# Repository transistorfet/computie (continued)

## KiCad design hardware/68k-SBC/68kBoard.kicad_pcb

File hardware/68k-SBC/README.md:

68k-SBC
=======

Status: Built & Tested

Latest: Rev.2

### About
A single board computer with DIP packaged chips.  The only programmable chip is the flash memory, which can
be written in-circuit using the Ardunio-based supervisor shield.

[Revision 2 Notes & Errata](revisions/68kBoard-rev2-errata.txt)

[Revision 2 Schematic](revisions/68kBoard-rev2.pdf)

[Revision 2 Gerbers](revisions/68kBoard-rev2.zip)

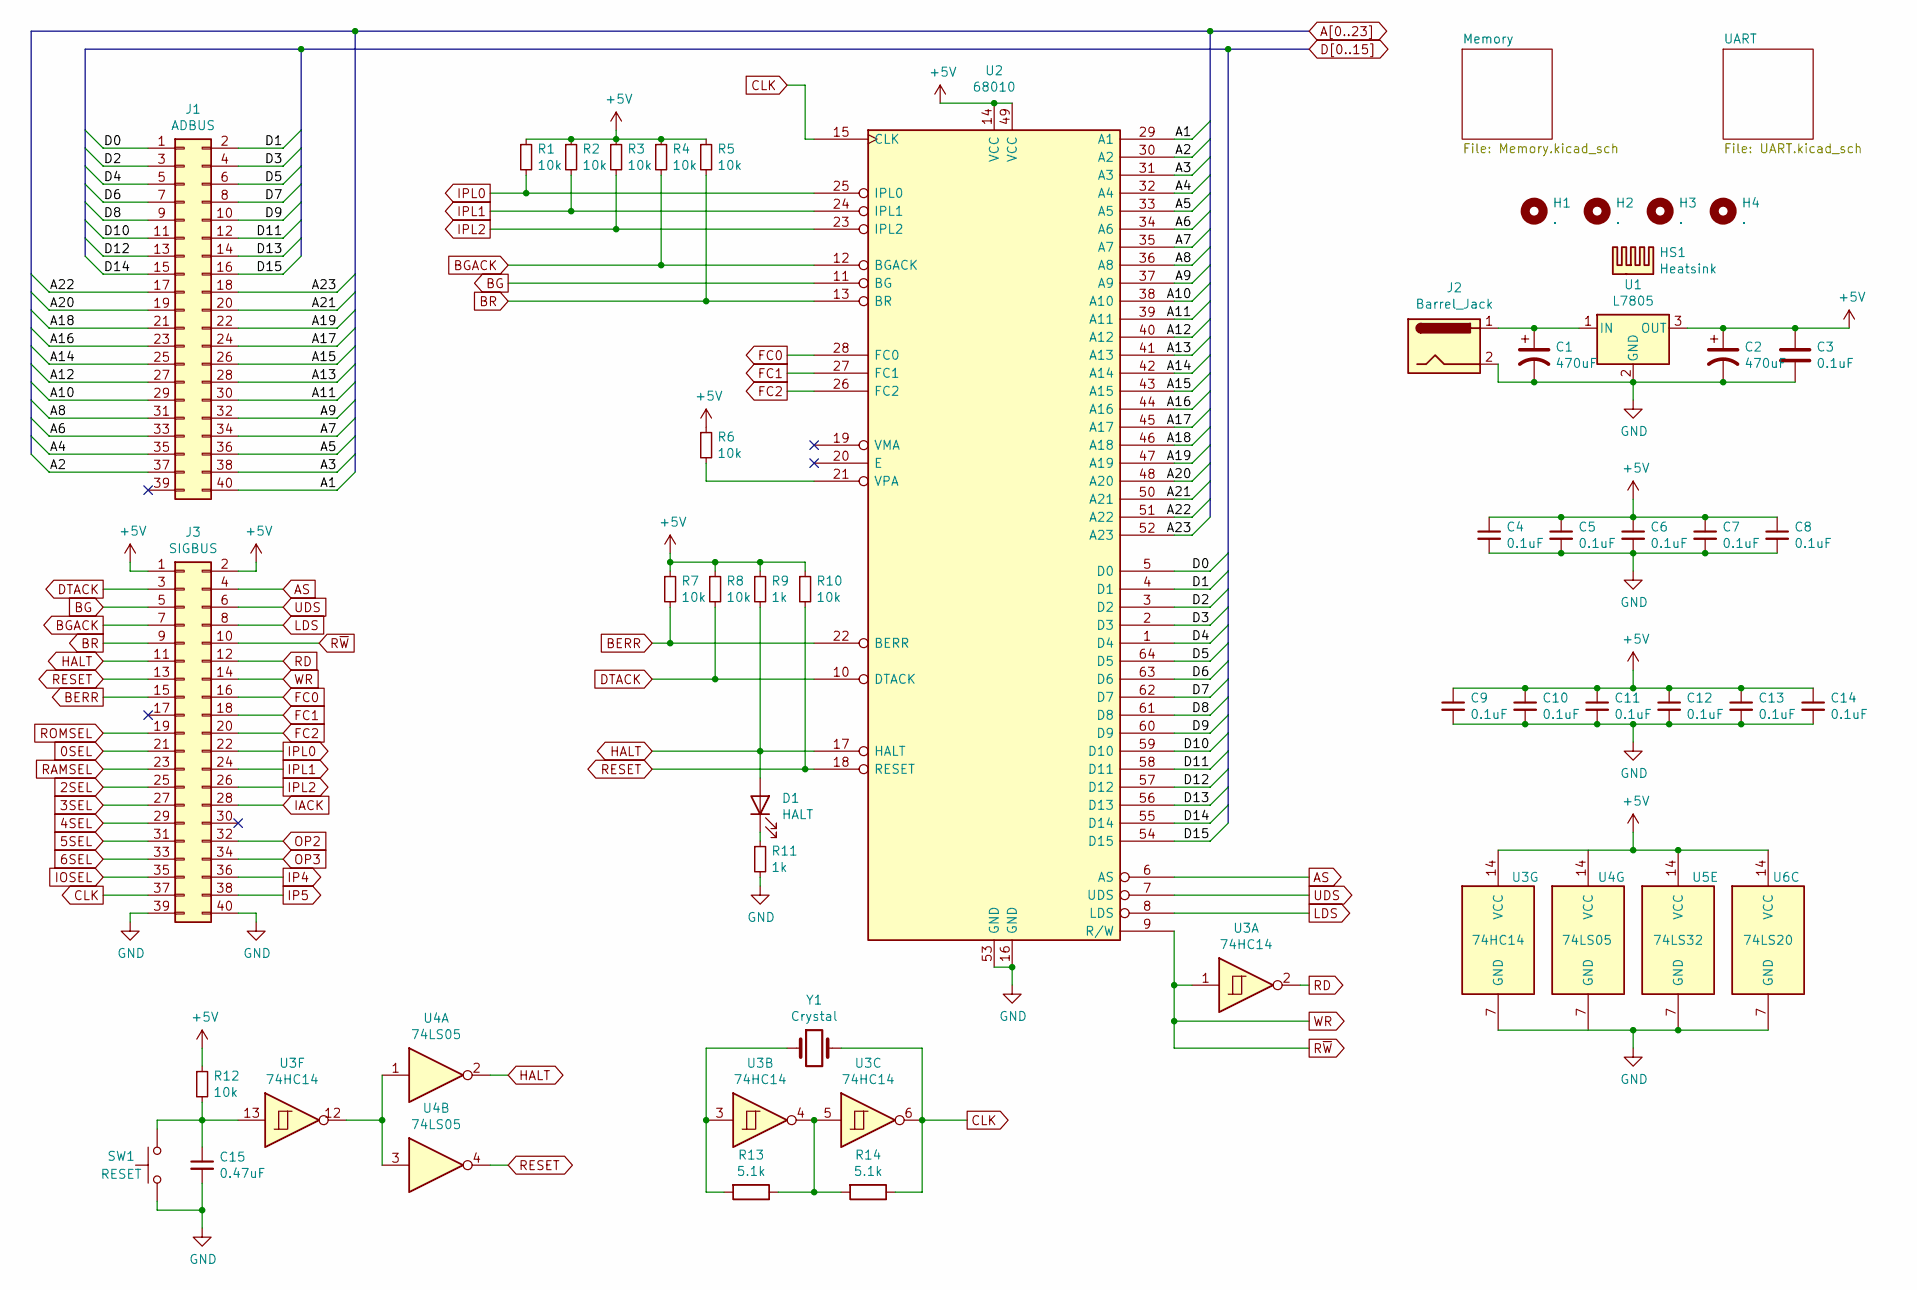
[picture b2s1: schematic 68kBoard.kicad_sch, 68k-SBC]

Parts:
C1, C2: 470uF; CP_Radial_D10.0mm_P5.00mm
C3, C4, C5, C6, C7, C8, C9, C10, C11, C12, C13, C14: 0.1uF; C_Disc_D3.0mm_W2.0mm_P2.50mm
C15: 0.47uF; C_Disc_D3.0mm_W2.0mm_P2.50mm
D1: HALT; LED_D5.0mm
H1, H2, H3, H4: .; MountingHole_2.7mm_Pad_Via
HS1: Heatsink; Heatsink_Fischer_SK104-STC-STIC_35x13mm_2xDrill2.5mm
J1: ADBUS; PinHeader_2x20_P2.54mm_Vertical
J2: Barrel_Jack; BarrelJack_Horizontal
J3: SIGBUS; PinHeader_2x20_P2.54mm_Vertical
R1, R2, R3, R4, R5, R6, R7, R8, R10, R12: 10k; R_Axial_DIN0207_L6.3mm_D2.5mm_P7.62mm_Horizontal
R9, R11: 1k; R_Axial_DIN0207_L6.3mm_D2.5mm_P7.62mm_Horizontal
R13, R14: 5.1k; R_Axial_DIN0207_L6.3mm_D2.5mm_P7.62mm_Horizontal
SW1: RESET; SW_PUSH_6mm
U1: L7805; TO-220-3_Vertical
U2: 68010; DIP-64_W22.86mm_Socket_LongPads
U3: 74HC14; DIP-14_W7.62mm_LongPads
U4: 74LS05; DIP-14_W7.62mm_LongPads
U5: 74LS32; DIP-14_W7.62mm_LongPads
U6: 74LS20; DIP-14_W7.62mm_LongPads
Y1: Crystal; Crystal_HC49-4H_Vertical

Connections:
0SEL: J3.21; also elsewhere on the board
2SEL: J3.25; also elsewhere on the board
3SEL: J3.27; also elsewhere on the board
4SEL: J3.29; also elsewhere on the board
5SEL: J3.31; also elsewhere on the board
6SEL: J3.33; also elsewhere on the board
+5V: C2.1, C3.1, C4.1, C5.1, C6.1, C7.1, C8.1, C9.1, C10.1, C11.1, C12.1, C13.1, C14.1, J3.1, J3.2, R1.1, R2.1, R3.1, R4.1, R5.1, R6.1, R7.1, R8.1, R9.1, R10.1, R12.1, U1.3 (OUT), U2.14 (VCC), U2.49 (VCC), U3.14 (VCC), U4.14 (VCC), U5.14 (VCC), U6.14 (VCC); also elsewhere on the board
A1: J1.40, U2.29 (A1); also elsewhere on the board
A2: J1.37, U2.30 (A2); also elsewhere on the board
A3: J1.38, U2.31 (A3); also elsewhere on the board
A4: J1.35, U2.32 (A4); also elsewhere on the board
A5: J1.36, U2.33 (A5); also elsewhere on the board
A6: J1.33, U2.34 (A6); also elsewhere on the board
A7: J1.34, U2.35 (A7); also elsewhere on the board
A8: J1.31, U2.36 (A8); also elsewhere on the board
A9: J1.32, U2.37 (A9); also elsewhere on the board
A10: J1.29, U2.38 (A10); also elsewhere on the board
A11: J1.30, U2.39 (A11); also elsewhere on the board
A12: J1.27, U2.40 (A12); also elsewhere on the board
A13: J1.28, U2.41 (A13); also elsewhere on the board
A14: J1.25, U2.42 (A14); also elsewhere on the board
A15: J1.26, U2.43 (A15); also elsewhere on the board
A16: J1.23, U2.44 (A16); also elsewhere on the board
A17: J1.24, U2.45 (A17); also elsewhere on the board
A18: J1.21, U2.46 (A18); also elsewhere on the board
A19: J1.22, U2.47 (A19); also elsewhere on the board
A20: J1.19, U2.48 (A20); also elsewhere on the board
A21: J1.20, U2.50 (A21); also elsewhere on the board
A22: J1.17, U2.51 (A22); also elsewhere on the board
A23: J1.18, U2.52 (A23); also elsewhere on the board
AS: J3.4, U2.6 (AS); also elsewhere on the board
BERR: J3.15, R7.2, U2.22 (BERR)
BG: J3.5, U2.11 (BG)
BGACK: J3.7, R4.2, U2.12 (BGACK)
BR: J3.9, R5.2, U2.13 (BR)
CLK: J3.37, R14.1, U2.15 (CLK), U3.6, Y1.2
D0: J1.1, U2.5 (D0); also elsewhere on the board
D1: J1.2, U2.4 (D1); also elsewhere on the board
D2: J1.3, U2.3 (D2); also elsewhere on the board
D3: J1.4, U2.2 (D3); also elsewhere on the board
D4: J1.5, U2.1 (D4); also elsewhere on the board
D5: J1.6, U2.64 (D5); also elsewhere on the board
D6: J1.7, U2.63 (D6); also elsewhere on the board
D7: J1.8, U2.62 (D7); also elsewhere on the board
D8: J1.9, U2.61 (D8); also elsewhere on the board
D9: J1.10, U2.60 (D9); also elsewhere on the board
D10: J1.11, U2.59 (D10); also elsewhere on the board
D11: J1.12, U2.58 (D11); also elsewhere on the board
D12: J1.13, U2.57 (D12); also elsewhere on the board
D13: J1.14, U2.56 (D13); also elsewhere on the board
D14: J1.15, U2.55 (D14); also elsewhere on the board
D15: J1.16, U2.54 (D15); also elsewhere on the board
DTACK: J3.3, R8.2, U2.10 (DTACK); also elsewhere on the board
FC0: J3.16, U2.28 (FC0); also elsewhere on the board
FC1: J3.18, U2.27 (FC1); also elsewhere on the board
FC2: J3.20, U2.26 (FC2); also elsewhere on the board
GND: C1.2, C2.2, C3.2, C4.2, C5.2, C6.2, C7.2, C8.2, C9.2, C10.2, C11.2, C12.2, C13.2, C14.2, C15.2, J2.2, J3.39, J3.40, R11.2, SW1.1, U1.2 (GND), U2.16 (GND), U2.53 (GND), U3.7 (GND), U4.7 (GND), U5.7 (GND), U6.7 (GND); also elsewhere on the board
HALT: D1.2 (A), J3.11, R9.2, U2.17 (HALT), U4.2
IACK: J3.28; also elsewhere on the board
IOSEL: J3.35; also elsewhere on the board
IP4: J3.36; also elsewhere on the board
IP5: J3.38; also elsewhere on the board
IPL0: J3.22, R1.2, U2.25 (IPL0)
IPL1: J3.24, R2.2, U2.24 (IPL1); also elsewhere on the board
IPL2: J3.26, R3.2, U2.23 (IPL2)
LDS: J3.8, U2.8 (LDS); also elsewhere on the board
unnamed: C1.1, J2.1, U1.1 (IN)
unnamed: C15.1, R12.2, SW1.2, U3.13
unnamed: D1.1 (K), R11.1
unnamed: R6.2, U2.21 (VPA)
unnamed: R13.1, R14.2, U3.4, U3.5
unnamed: R13.2, U3.3, Y1.1
unnamed: U3.12, U4.1, U4.3
OP2: J3.32; also elsewhere on the board
OP3: J3.34; also elsewhere on the board
RAMSEL: J3.23; also elsewhere on the board
RD: J3.12, U3.2; also elsewhere on the board
RESET: J3.13, R10.2, U2.18 (RESET), U4.4; also elsewhere on the board
ROMSEL: J3.19; also elsewhere on the board
R~W: J3.10, J3.14, U2.9 (R/W), U3.1; also elsewhere on the board
UDS: J3.6, U2.7 (UDS); also elsewhere on the board

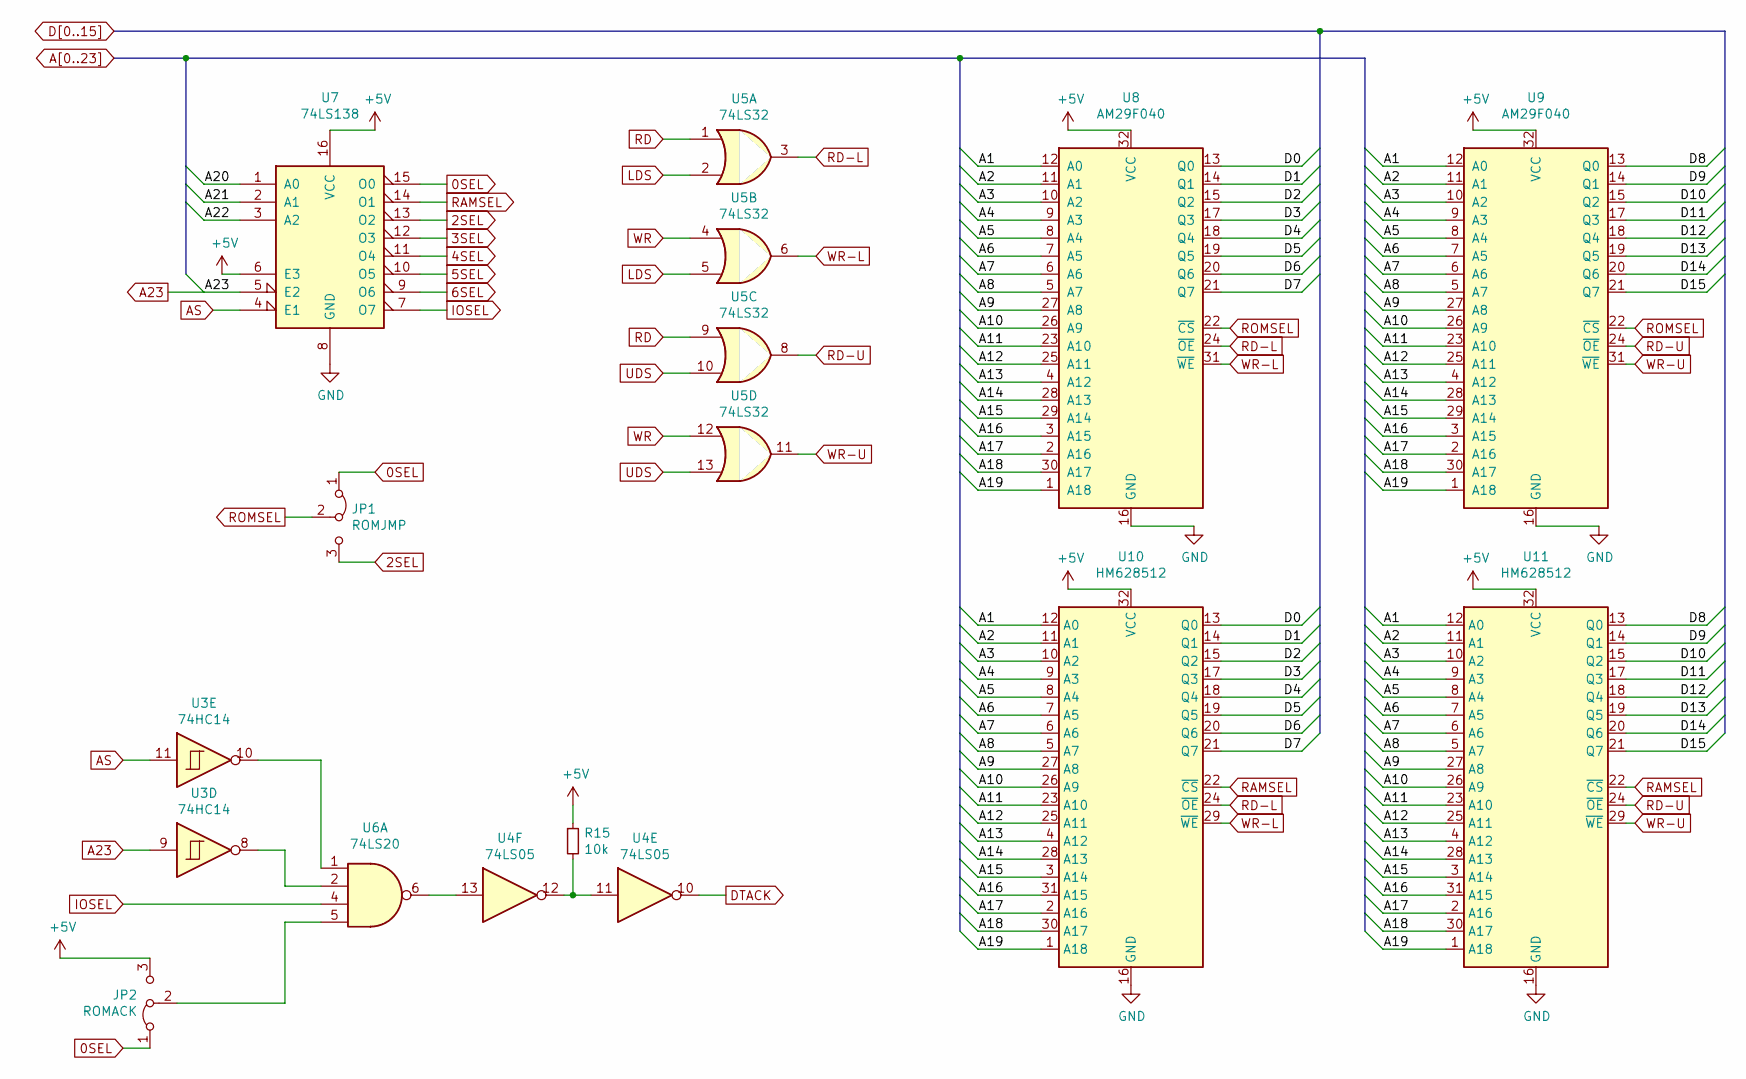
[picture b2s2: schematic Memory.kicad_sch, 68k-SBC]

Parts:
JP1: ROMJMP; PinHeader_1x03_P2.54mm_Vertical
JP2: ROMACK; PinHeader_1x03_P2.54mm_Vertical
R15: 10k; R_Axial_DIN0207_L6.3mm_D2.5mm_P7.62mm_Horizontal
U3: 74HC14; DIP-14_W7.62mm_LongPads
U4: 74LS05; DIP-14_W7.62mm_LongPads
U5: 74LS32; DIP-14_W7.62mm_LongPads
U6: 74LS20; DIP-14_W7.62mm_LongPads
U7: 74LS138; DIP-16_W7.62mm_LongPads
U8, U9: AM29F040; DIP-32_W15.24mm_Socket_LongPads
U10, U11: HM628512; DIP-32_W15.24mm_Socket_LongPads

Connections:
0SEL: JP1.1 (A), JP2.1 (A), U7.15 (O0); also elsewhere on the board
2SEL: JP1.3 (B), U7.13 (O2); also elsewhere on the board
3SEL: U7.12 (O3); also elsewhere on the board
4SEL: U7.11 (O4); also elsewhere on the board
5SEL: U7.10 (O5); also elsewhere on the board
6SEL: U7.9 (O6); also elsewhere on the board
+5V: JP2.3 (B), R15.1, U7.6 (E3), U7.16 (VCC), U8.32 (VCC), U9.32 (VCC), U10.32 (VCC), U11.32 (VCC); also elsewhere on the board
A1: U8.12 (A0), U9.12 (A0), U10.12 (A0), U11.12 (A0); also elsewhere on the board
A2: U8.11 (A1), U9.11 (A1), U10.11 (A1), U11.11 (A1); also elsewhere on the board
A3: U8.10 (A2), U9.10 (A2), U10.10 (A2), U11.10 (A2); also elsewhere on the board
A4: U8.9 (A3), U9.9 (A3), U10.9 (A3), U11.9 (A3); also elsewhere on the board
A5: U8.8 (A4), U9.8 (A4), U10.8 (A4), U11.8 (A4); also elsewhere on the board
A6: U8.7 (A5), U9.7 (A5), U10.7 (A5), U11.7 (A5); also elsewhere on the board
A7: U8.6 (A6), U9.6 (A6), U10.6 (A6), U11.6 (A6); also elsewhere on the board
A8: U8.5 (A7), U9.5 (A7), U10.5 (A7), U11.5 (A7); also elsewhere on the board
A9: U8.27 (A8), U9.27 (A8), U10.27 (A8), U11.27 (A8); also elsewhere on the board
A10: U8.26 (A9), U9.26 (A9), U10.26 (A9), U11.26 (A9); also elsewhere on the board
A11: U8.23 (A10), U9.23 (A10), U10.23 (A10), U11.23 (A10); also elsewhere on the board
A12: U8.25 (A11), U9.25 (A11), U10.25 (A11), U11.25 (A11); also elsewhere on the board
A13: U8.4 (A12), U9.4 (A12), U10.4 (A12), U11.4 (A12); also elsewhere on the board
A14: U8.28 (A13), U9.28 (A13), U10.28 (A13), U11.28 (A13); also elsewhere on the board
A15: U8.29 (A14), U9.29 (A14), U10.3 (A14), U11.3 (A14); also elsewhere on the board
A16: U8.3 (A15), U9.3 (A15), U10.31 (A15), U11.31 (A15); also elsewhere on the board
A17: U8.2 (A16), U9.2 (A16), U10.2 (A16), U11.2 (A16); also elsewhere on the board
A18: U8.30 (A17), U9.30 (A17), U10.30 (A17), U11.30 (A17); also elsewhere on the board
A19: U8.1 (A18), U9.1 (A18), U10.1 (A18), U11.1 (A18); also elsewhere on the board
A20: U7.1 (A0); also elsewhere on the board
A21: U7.2 (A1); also elsewhere on the board
A22: U7.3 (A2); also elsewhere on the board
A23: U3.9, U7.5 (E2); also elsewhere on the board
AS: U3.11, U7.4 (E1); also elsewhere on the board
D0: U8.13 (Q0), U10.13 (Q0); also elsewhere on the board
D1: U8.14 (Q1), U10.14 (Q1); also elsewhere on the board
D2: U8.15 (Q2), U10.15 (Q2); also elsewhere on the board
D3: U8.17 (Q3), U10.17 (Q3); also elsewhere on the board
D4: U8.18 (Q4), U10.18 (Q4); also elsewhere on the board
D5: U8.19 (Q5), U10.19 (Q5); also elsewhere on the board
D6: U8.20 (Q6), U10.20 (Q6); also elsewhere on the board
D7: U8.21 (Q7), U10.21 (Q7); also elsewhere on the board
D8: U9.13 (Q0), U11.13 (Q0); also elsewhere on the board
D9: U9.14 (Q1), U11.14 (Q1); also elsewhere on the board
D10: U9.15 (Q2), U11.15 (Q2); also elsewhere on the board
D11: U9.17 (Q3), U11.17 (Q3); also elsewhere on the board
D12: U9.18 (Q4), U11.18 (Q4); also elsewhere on the board
D13: U9.19 (Q5), U11.19 (Q5); also elsewhere on the board
D14: U9.20 (Q6), U11.20 (Q6); also elsewhere on the board
D15: U9.21 (Q7), U11.21 (Q7); also elsewhere on the board
DTACK: U4.10; also elsewhere on the board
GND: U7.8 (GND), U8.16 (GND), U9.16 (GND), U10.16 (GND), U11.16 (GND); also elsewhere on the board
IOSEL: U6.4, U7.7 (O7); also elsewhere on the board
LDS: U5.2, U5.5; also elsewhere on the board
unnamed: JP2.2 (C), U6.5
unnamed: R15.2, U4.11, U4.12
unnamed: U3.8, U6.2
unnamed: U3.10, U6.1
unnamed: U4.13, U6.6
RAMSEL: U7.14 (O1), U10.22 (~CS), U11.22 (~CS); also elsewhere on the board
RD: U5.1, U5.9; also elsewhere on the board
RD-L: U5.3, U8.24 (~OE), U10.24 (~OE)
RD-U: U5.8, U9.24 (~OE), U11.24 (~OE)
ROMSEL: JP1.2 (C), U8.22 (~CS), U9.22 (~CS); also elsewhere on the board
R~W: U5.4, U5.12; also elsewhere on the board
UDS: U5.10, U5.13; also elsewhere on the board
WR-L: U5.6, U8.31 (~WE), U10.29 (~WE)
WR-U: U5.11, U9.31 (~WE), U11.29 (~WE)

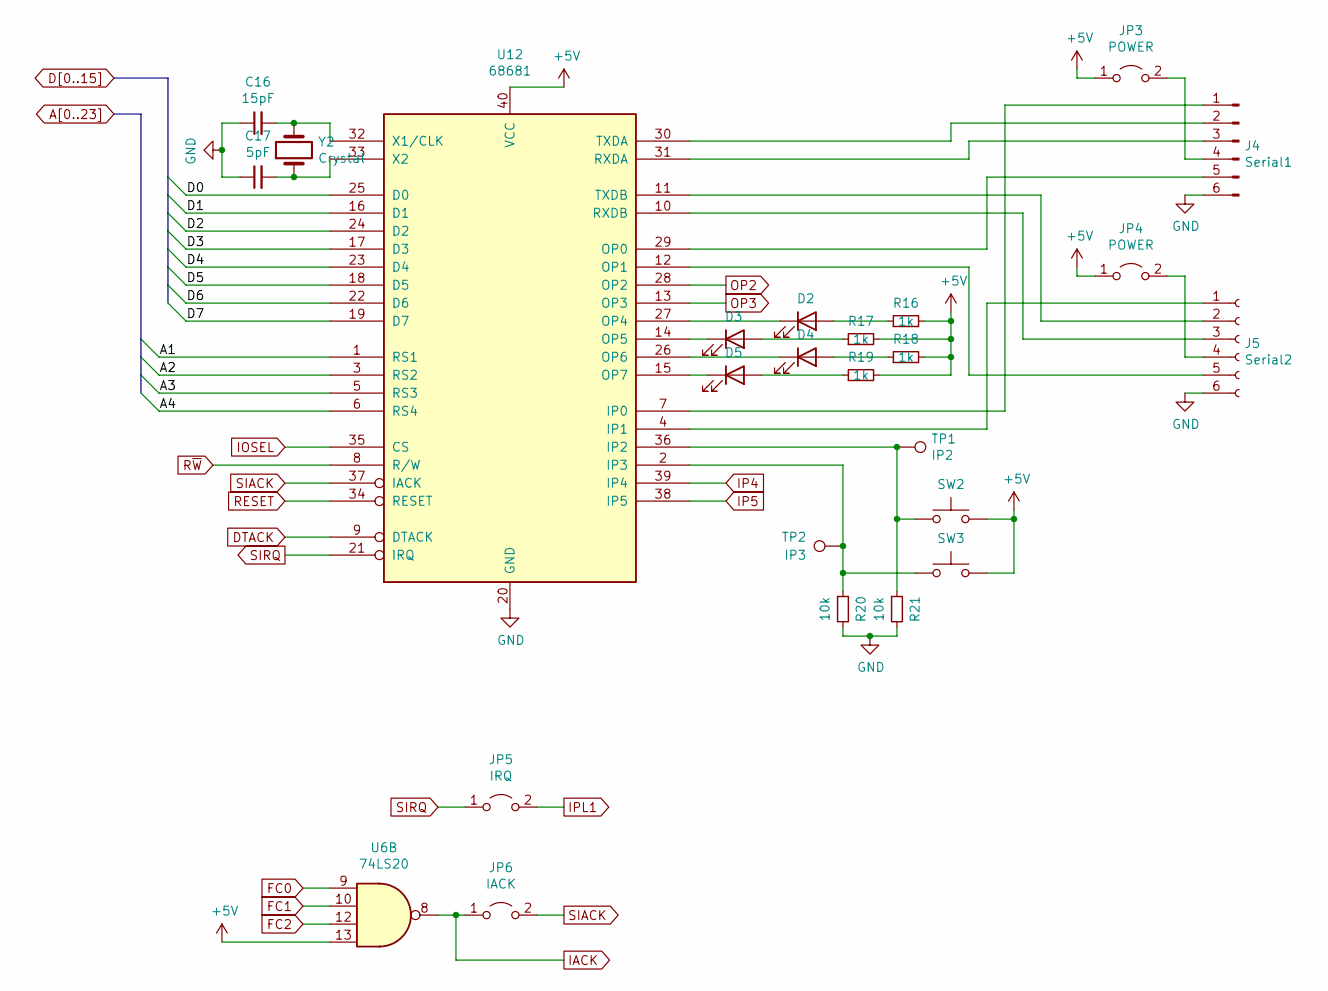
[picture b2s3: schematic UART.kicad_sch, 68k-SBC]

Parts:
C16: 15pF; C_Disc_D3.0mm_W2.0mm_P2.50mm
C17: 5pF; C_Disc_D3.0mm_W2.0mm_P2.50mm
D2: OP4; LED_D5.0mm
D3: OP5; LED_D5.0mm
D4: OP6; LED_D5.0mm
D5: OP7; LED_D5.0mm
J4: Serial1; PinHeader_1x06_P2.54mm_Horizontal
J5: Serial2; PinHeader_1x06_P2.54mm_Horizontal
JP3, JP4: POWER; PinHeader_1x02_P2.54mm_Vertical
JP5: IRQ; PinHeader_1x02_P2.54mm_Vertical
JP6: IACK; PinHeader_1x02_P2.54mm_Vertical
R16, R17, R18, R19: 1k; R_Axial_DIN0207_L6.3mm_D2.5mm_P7.62mm_Horizontal
R20, R21: 10k; R_Axial_DIN0207_L6.3mm_D2.5mm_P7.62mm_Horizontal
SW2: IP2; SW_PUSH_6mm
SW3: IP3; SW_PUSH_6mm
TP1: IP2; TestPoint_THTPad_2.0x2.0mm_Drill1.0mm
TP2: IP3; TestPoint_THTPad_2.0x2.0mm_Drill1.0mm
U6: 74LS20; DIP-14_W7.62mm_LongPads
U12: 68681; DIP-40_W15.24mm_Socket_LongPads
Y2: Crystal; Crystal_HC49-4H_Vertical

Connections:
+5V: JP3.1 (A), JP4.1 (A), R16.2, R17.2, R18.2, R19.2, SW2.2, SW3.2, U6.13, U12.40 (VCC); also elsewhere on the board
A1: U12.1 (RS1); also elsewhere on the board
A2: U12.3 (RS2); also elsewhere on the board
A3: U12.5 (RS3); also elsewhere on the board
A4: U12.6 (RS4); also elsewhere on the board
D0: U12.25 (D0); also elsewhere on the board
D1: U12.16 (D1); also elsewhere on the board
D2: U12.24 (D2); also elsewhere on the board
D3: U12.17 (D3); also elsewhere on the board
D4: U12.23 (D4); also elsewhere on the board
D5: U12.18 (D5); also elsewhere on the board
D6: U12.22 (D6); also elsewhere on the board
D7: U12.19 (D7); also elsewhere on the board
DTACK: U12.9 (DTACK); also elsewhere on the board
FC0: U6.9; also elsewhere on the board
FC1: U6.10; also elsewhere on the board
FC2: U6.12; also elsewhere on the board
GND: C16.1, C17.1, J4.6, J5.6, R20.2, R21.2, U12.20 (GND); also elsewhere on the board
IACK: JP6.1 (A), U6.8; also elsewhere on the board
IOSEL: U12.35 (CS); also elsewhere on the board
IP4: U12.39 (IP4); also elsewhere on the board
IP5: U12.38 (IP5); also elsewhere on the board
IPL1: JP5.2 (B); also elsewhere on the board
unnamed: C16.2, U12.32 (X1/CLK), Y2.2
unnamed: C17.2, U12.33 (X2), Y2.1
unnamed: D2.1 (K), U12.27 (OP4)
unnamed: D2.2 (A), R16.1
unnamed: D3.1 (K), U12.14 (OP5)
unnamed: D3.2 (A), R17.1
unnamed: D4.1 (K), U12.26 (OP6)
unnamed: D4.2 (A), R18.1
unnamed: D5.1 (K), U12.15 (OP7)
unnamed: D5.2 (A), R19.1
unnamed: J4.1, U12.7 (IP0)
unnamed: J4.2, U12.30 (TXDA)
unnamed: J4.3, U12.31 (RXDA)
unnamed: J4.4, JP3.2 (B)
unnamed: J4.5, U12.29 (OP0)
unnamed: J5.1, U12.4 (IP1)
unnamed: J5.2, U12.11 (TXDB)
unnamed: J5.3, U12.10 (RXDB)
unnamed: J5.4, JP4.2 (B)
unnamed: J5.5, U12.12 (OP1)
unnamed: R20.1, SW3.1, TP2.1, U12.2 (IP3)
unnamed: R21.1, SW2.1, TP1.1, U12.36 (IP2)
OP2: U12.28 (OP2); also elsewhere on the board
OP3: U12.13 (OP3); also elsewhere on the board
RESET: U12.34 (RESET); also elsewhere on the board
R~W: U12.8 (R/W); also elsewhere on the board
SIACK: JP6.2 (B), U12.37 (IACK)
SIRQ: JP5.1 (A), U12.21 (IRQ)

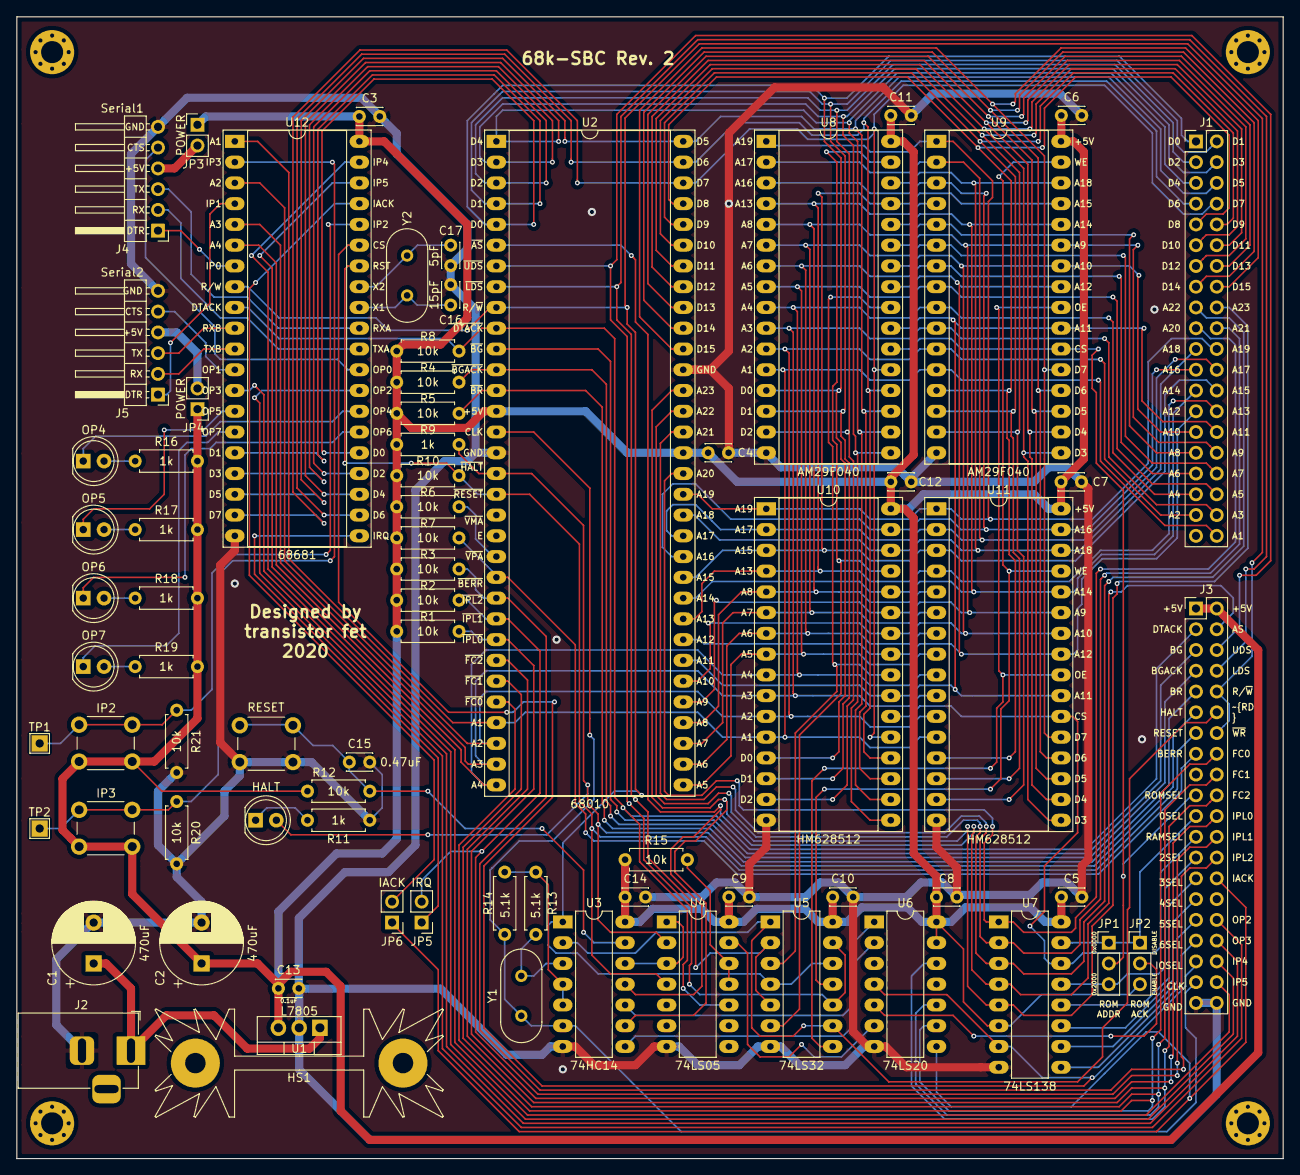
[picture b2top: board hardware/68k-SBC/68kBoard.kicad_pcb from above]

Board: 2 copper layers, 154.9 x 139.7 mm, 78 parts (0 on the bottom side), 114 nets.

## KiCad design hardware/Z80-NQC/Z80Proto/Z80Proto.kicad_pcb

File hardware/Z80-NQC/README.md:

The Z80 Not Quite Computer
==========================

A simple platform for experimenting with Z80 CPUs.  The Z80Proto board has a Z80 CPU, with a 32KB SRAM chip and a 32KB EEPROM
chip, along with a bus of pins for connecting to other things.  It also has a simple clock circuit that can optionally be used.
It does not have any onboard I/O, or an onboard power supply (hence why it's not quite a computer).  The intention is to connect
the bus pins to an Arduino Mega, which acts as a supervisor, controlling the CPU through the BUSREQ and RESET lines, and
emulating I/O devices.  It was made partly to try out some 3rd party PCB manufacturers and partly because of signal issues when
breadboarding circuits with so many wires, which was causing memory read errors.

Z80Supervisor is an arduino program which can run or stop the CPU, and read and write to memory directly (when the CPU is
suspended).  It is also able to respond to memory bus requests from the CPU, as long as the CPU is running with a slow clock.
It can both act as a ROM, serving up a Z80 program, and act as an I/O device by forwarding bytes on to the arduino's serial
port.

Z80Monitor contains programs that run on the Z80, which can either be loaded into the EEPROM, or served by the supervisor.

Schematic
---------

Board
-----

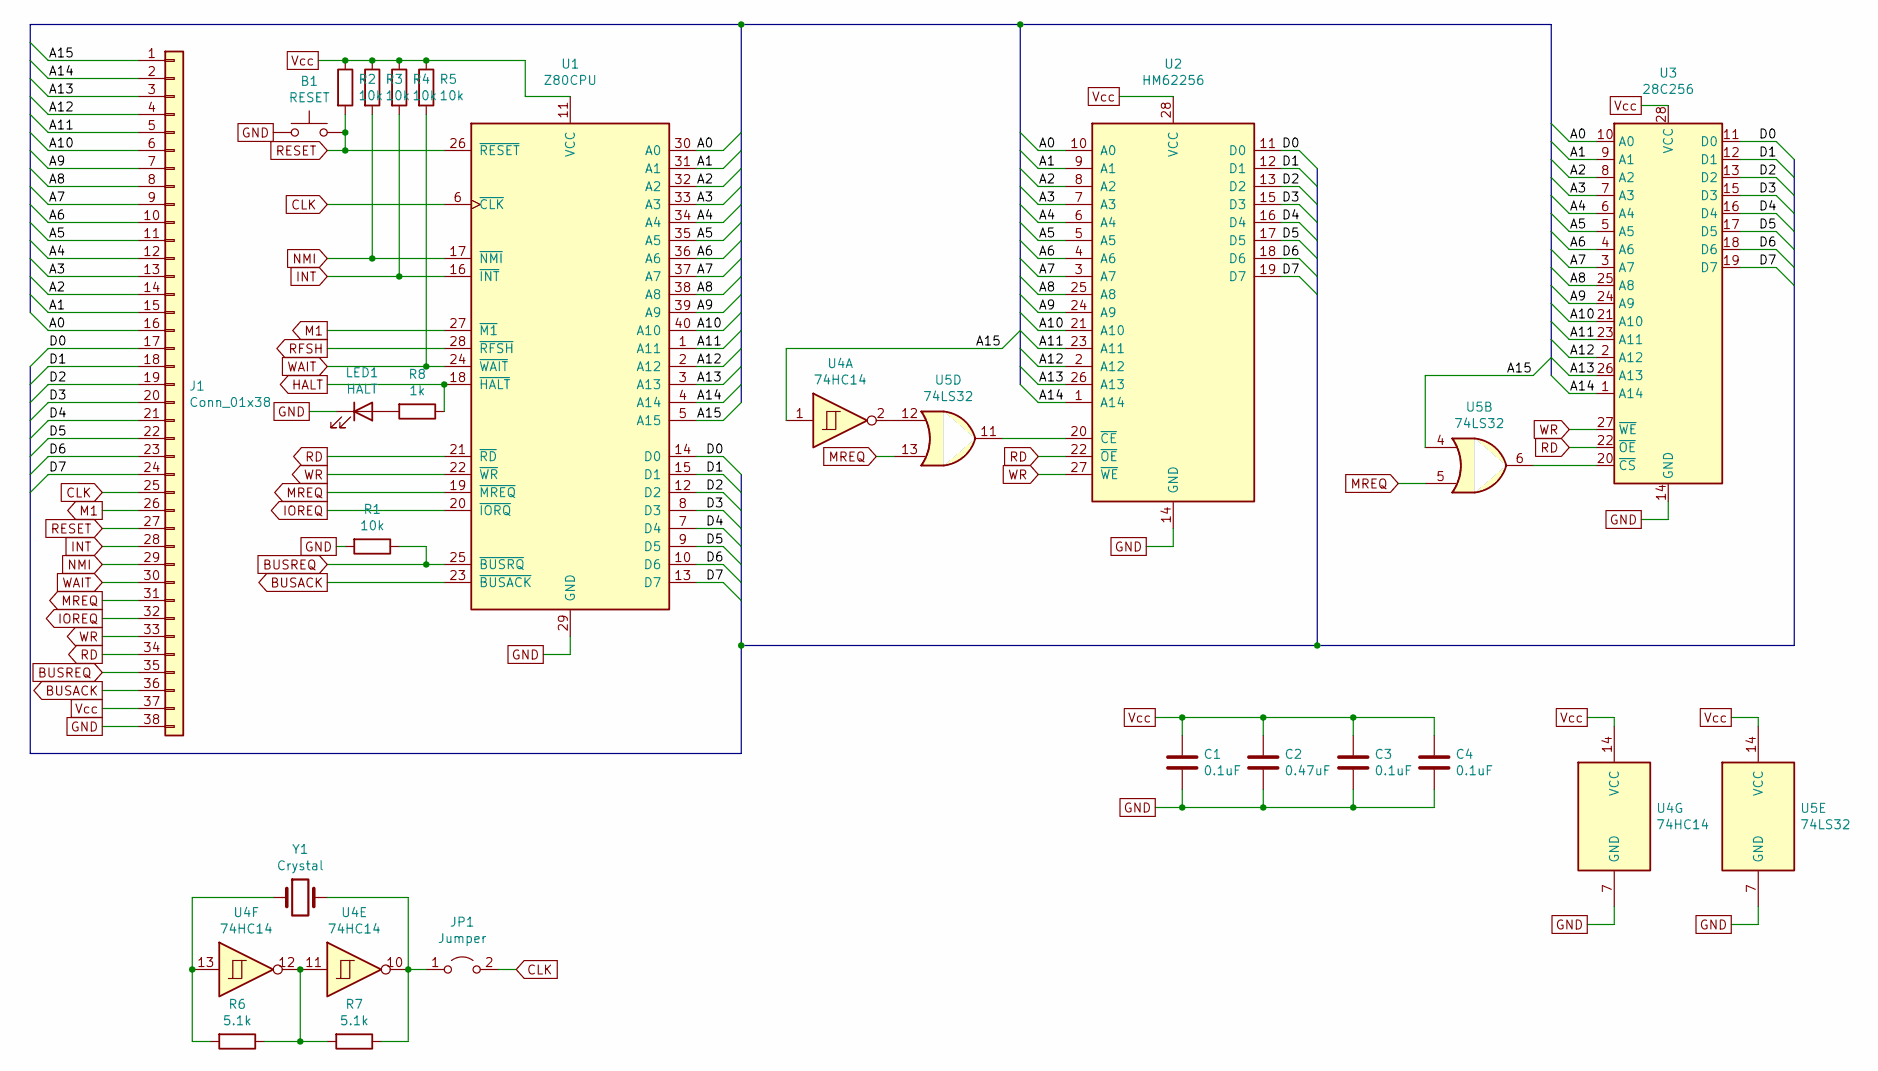
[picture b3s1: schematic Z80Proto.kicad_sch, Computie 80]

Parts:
B1: RESET; SW_PUSH_6mm
C1, C3, C4: 0.1uF; C_Disc_D3.0mm_W2.0mm_P2.50mm
C2: 0.47uF; C_Disc_D3.0mm_W2.0mm_P2.50mm
J1: Conn_01x38; PinHeader_1x38_P2.54mm_Vertical
JP1: Jumper; PinHeader_1x02_P2.54mm_Vertical
LED1: HALT; LED_D5.0mm
R1, R2, R3, R4, R5: 10k; R_Axial_DIN0207_L6.3mm_D2.5mm_P7.62mm_Horizontal
R6, R7: 5.1k; R_Axial_DIN0207_L6.3mm_D2.5mm_P7.62mm_Horizontal
R8: 1k; R_Axial_DIN0207_L6.3mm_D2.5mm_P7.62mm_Horizontal
U1: Z80CPU; DIP-40_W15.24mm
U2: HM62256; DIP-28_W15.24mm_Socket
U3: 28C256; DIP-28_W15.24mm_Socket
U4: 74HC14; DIP-14_W7.62mm
U5: 74LS32; DIP-14_W7.62mm
Y1: Crystal; Crystal_HC49-4H_Vertical

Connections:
/A0: J1.16, U1.30 (A0), U2.10 (A0), U3.10 (A0); also elsewhere on the board
/A1: J1.15, U1.31 (A1), U2.9 (A1), U3.9 (A1); also elsewhere on the board
/A2: J1.14, U1.32 (A2), U2.8 (A2), U3.8 (A2); also elsewhere on the board
/A3: J1.13, U1.33 (A3), U2.7 (A3), U3.7 (A3); also elsewhere on the board
/A4: J1.12, U1.34 (A4), U2.6 (A4), U3.6 (A4); also elsewhere on the board
/A5: J1.11, U1.35 (A5), U2.5 (A5), U3.5 (A5); also elsewhere on the board
/A6: J1.10, U1.36 (A6), U2.4 (A6), U3.4 (A6); also elsewhere on the board
/A7: J1.9, U1.37 (A7), U2.3 (A7), U3.3 (A7); also elsewhere on the board
/A8: J1.8, U1.38 (A8), U2.25 (A8), U3.25 (A8); also elsewhere on the board
/A9: J1.7, U1.39 (A9), U2.24 (A9), U3.24 (A9); also elsewhere on the board
/A10: J1.6, U1.40 (A10), U2.21 (A10), U3.21 (A10); also elsewhere on the board
/A11: J1.5, U1.1 (A11), U2.23 (A11), U3.23 (A11); also elsewhere on the board
/A12: J1.4, U1.2 (A12), U2.2 (A12), U3.2 (A12); also elsewhere on the board
/A13: J1.3, U1.3 (A13), U2.26 (A13), U3.26 (A13); also elsewhere on the board
/A14: J1.2, U1.4 (A14), U2.1 (A14), U3.1 (A14); also elsewhere on the board
/A15: J1.1, U1.5 (A15), U4.1, U5.4; also elsewhere on the board
/D0: J1.17, U1.14 (D0), U2.11 (D0), U3.11 (D0); also elsewhere on the board
/D1: J1.18, U1.15 (D1), U2.12 (D1), U3.12 (D1); also elsewhere on the board
/D2: J1.19, U1.12 (D2), U2.13 (D2), U3.13 (D2); also elsewhere on the board
/D3: J1.20, U1.8 (D3), U2.15 (D3), U3.15 (D3); also elsewhere on the board
/D4: J1.21, U1.7 (D4), U2.16 (D4), U3.16 (D4); also elsewhere on the board
/D5: J1.22, U1.9 (D5), U2.17 (D5), U3.17 (D5); also elsewhere on the board
/D6: J1.23, U1.10 (D6), U2.18 (D6), U3.18 (D6); also elsewhere on the board
/D7: J1.24, U1.13 (D7), U2.19 (D7), U3.19 (D7); also elsewhere on the board
BUSACK: J1.36, U1.23 (~BUSACK); also elsewhere on the board
BUSREQ: J1.35, R1.1, U1.25 (~BUSRQ); also elsewhere on the board
CLK: J1.25, JP1.2 (B), U1.6 (~CLK); also elsewhere on the board
GND: B1.1, C1.2, C2.2, C3.2, C4.2, J1.38, LED1.1 (K), R1.2, U1.29 (GND), U2.14 (GND), U3.14 (GND), U4.7 (GND), U5.7 (GND); also elsewhere on the board
HALT: R8.1, U1.18 (~HALT)
INT: J1.28, R4.2, U1.16 (~INT); also elsewhere on the board
IOREQ: J1.32, U1.20 (~IORQ); also elsewhere on the board
M1: J1.26, U1.27 (~M1); also elsewhere on the board
MREQ: J1.31, U1.19 (~MREQ), U5.5, U5.13; also elsewhere on the board
NMI: J1.29, R3.2, U1.17 (~NMI); also elsewhere on the board
unnamed: JP1.1 (A), R7.1, U4.10, Y1.2
unnamed: LED1.2 (A), R8.2
unnamed: R6.1, R7.2, U4.11, U4.12
unnamed: R6.2, U4.13, Y1.1
unnamed: U2.20 (~CE), U5.11
unnamed: U3.20 (~CS), U5.6
unnamed: U4.2, U5.12
RD: J1.34, U1.21 (~RD), U2.22 (~OE), U3.22 (~OE); also elsewhere on the board
RESET: B1.2, J1.27, R2.2, U1.26 (~RESET); also elsewhere on the board
RFSH: U1.28 (~RFSH)
Vcc: C1.1, C2.1, C3.1, C4.1, J1.37, R2.1, R3.1, R4.1, R5.1, U1.11 (VCC), U2.28 (VCC), U3.28 (VCC), U4.14 (VCC), U5.14 (VCC); also elsewhere on the board
WAIT: J1.30, R5.2, U1.24 (~WAIT); also elsewhere on the board
WR: J1.33, U1.22 (~WR), U2.27 (~WE), U3.27 (~WE); also elsewhere on the board

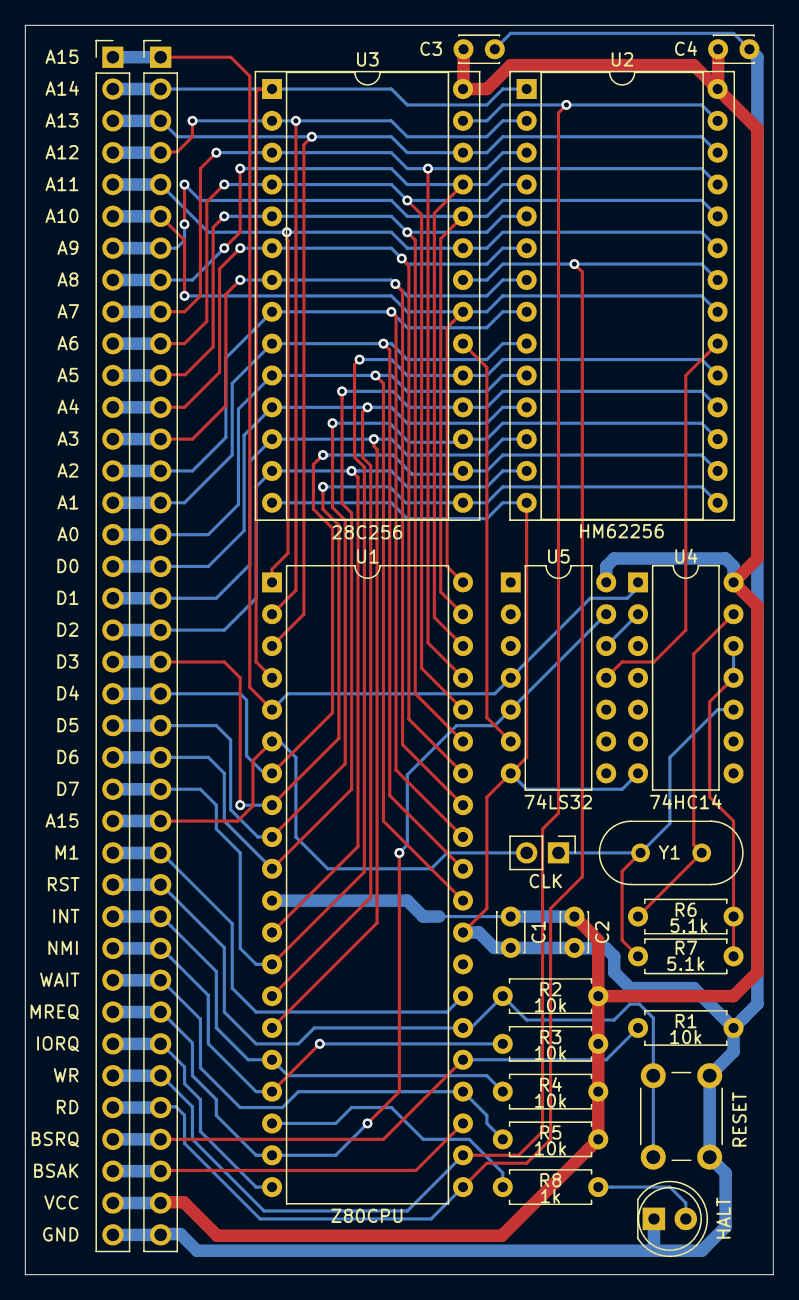
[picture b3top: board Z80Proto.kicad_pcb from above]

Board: 2 copper layers, 59.7 x 99.7 mm, 23 parts (0 on the bottom side), 46 nets.

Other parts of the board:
J1#2: Conn_01x38; PinHeader_1x38_P2.54mm_Vertical

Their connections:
/A0: J1#2.16; also elsewhere on the board
/A1: J1#2.15; also elsewhere on the board
/A2: J1#2.14; also elsewhere on the board
/A3: J1#2.13; also elsewhere on the board
/A4: J1#2.12; also elsewhere on the board
/A5: J1#2.11; also elsewhere on the board
/A6: J1#2.10; also elsewhere on the board
/A7: J1#2.9; also elsewhere on the board
/A8: J1#2.8; also elsewhere on the board
/A9: J1#2.7; also elsewhere on the board
/A10: J1#2.6; also elsewhere on the board
/A11: J1#2.5; also elsewhere on the board
/A12: J1#2.4; also elsewhere on the board
/A13: J1#2.3; also elsewhere on the board
/A14: J1#2.2; also elsewhere on the board
/A15: J1#2.1; also elsewhere on the board
/D0: J1#2.17; also elsewhere on the board
/D1: J1#2.18; also elsewhere on the board
/D2: J1#2.19; also elsewhere on the board
/D3: J1#2.20; also elsewhere on the board
/D4: J1#2.21; also elsewhere on the board
/D5: J1#2.22; also elsewhere on the board
/D6: J1#2.23; also elsewhere on the board
/D7: J1#2.24; also elsewhere on the board
BUSACK: J1#2.36; also elsewhere on the board
BUSREQ: J1#2.35; also elsewhere on the board
CLK: J1#2.25; also elsewhere on the board
GND: J1#2.38; also elsewhere on the board
INT: J1#2.28; also elsewhere on the board
IOREQ: J1#2.32; also elsewhere on the board
M1: J1#2.26; also elsewhere on the board
MREQ: J1#2.31; also elsewhere on the board
NMI: J1#2.29; also elsewhere on the board
RD: J1#2.34; also elsewhere on the board
RESET: J1#2.27; also elsewhere on the board
Vcc: J1#2.37; also elsewhere on the board
WAIT: J1#2.30; also elsewhere on the board
WR: J1#2.33; also elsewhere on the board
